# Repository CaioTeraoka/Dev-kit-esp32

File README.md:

# Dev Kit ESP32
This project is a board that was made with the purpose of being used to create and test simples projects using ESP32 DevKit. It was made to enthusiasts to have a complete board to play and have fun learning about ESP32. 

## Specifications:
**Power** - 5V <br>
**Stackup:**
1. Signal + 3.3V
2. Ground

## Main Components
- ESP32 DevKit <br>
- Buzzer <br>
- LEDs <br>
- Buttons <br>
- RGB LEDs <br>
- SPI Pin Headers <br>
- I2C Pin Headers <br>
- ADC Pin Headers <br>
- DAC Pin Headers <br>
- USART Pin Headers <br>
- PWM Pin Headers <br>

## 3D Model
 <br>

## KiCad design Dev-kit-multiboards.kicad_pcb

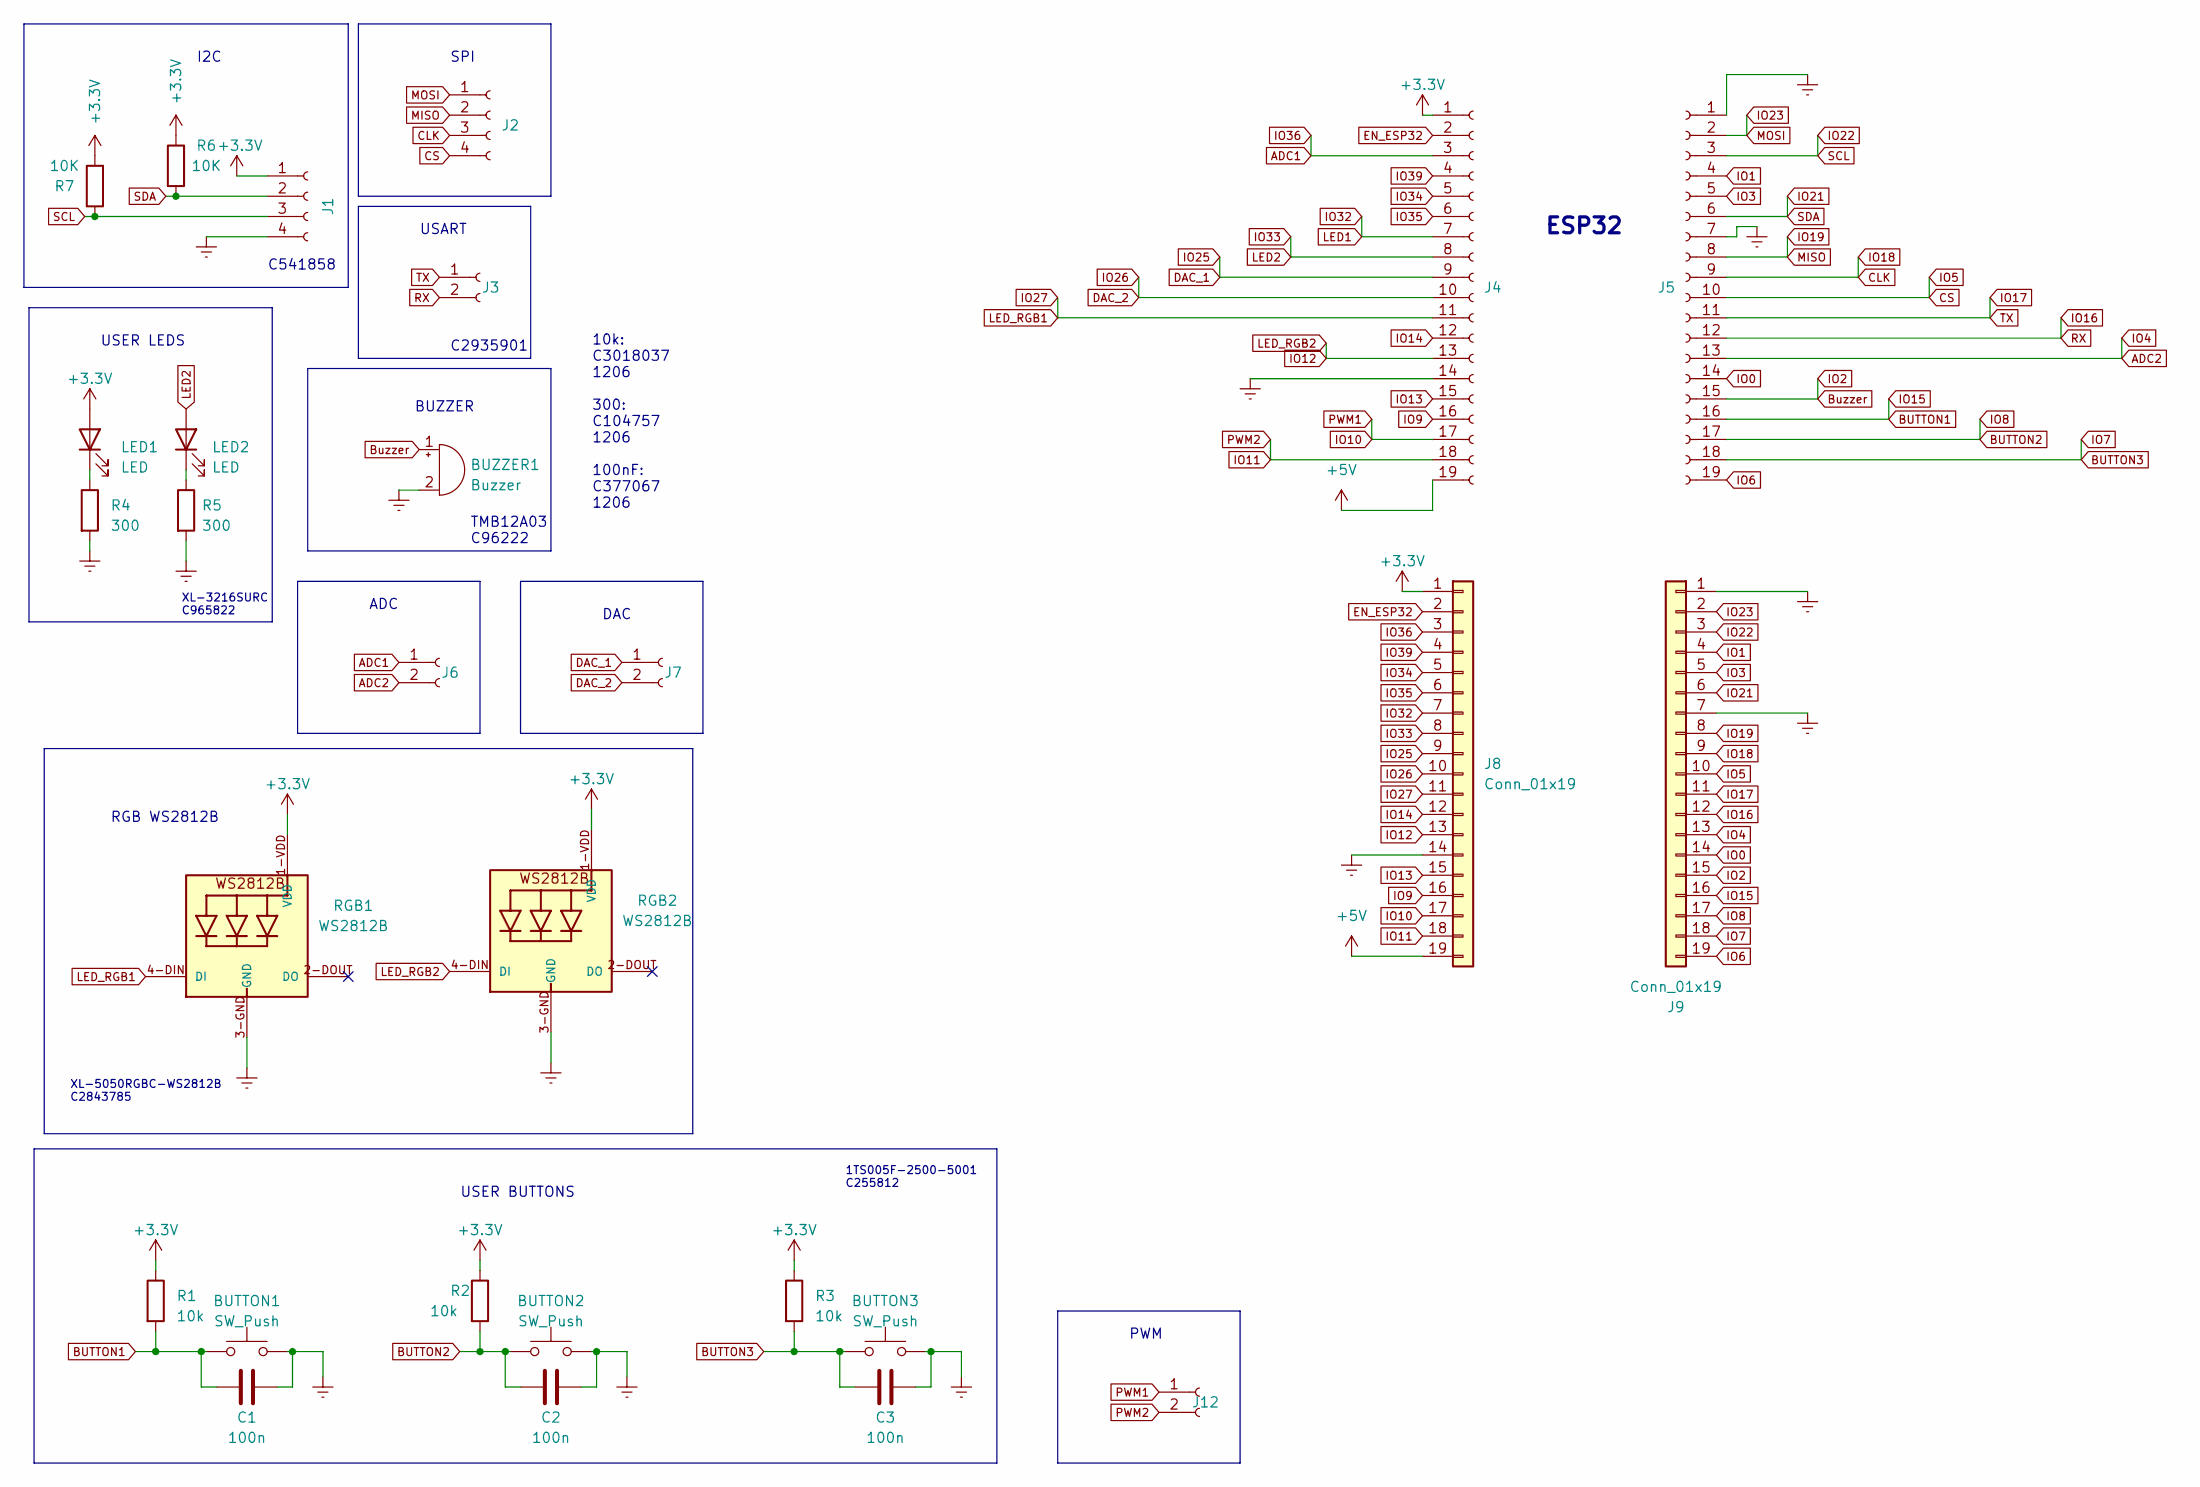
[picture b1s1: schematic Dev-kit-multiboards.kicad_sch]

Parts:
BUTTON1, BUTTON2, BUTTON3: SW_Push; SW_Push_1P1T_NO_6x6mm_H9.5mm
BUZZER1: Buzzer; Buzzer_12x9.5RM7.6
C1, C2, C3: 100n; C_1206_3216Metric
J1, J2: Conn_01x04_Socket; PinHeader_1x04_P2.54mm_Vertical
J3, J6, J7, J12: Conn_01x02_Socket; PinHeader_1x02_P2.54mm_Vertical
J4, J5: Conn_01x19_Socket; PinSocket_1x19_P2.54mm_Vertical
J8, J9: Conn_01x19; PinHeader_1x19_P2.54mm_Vertical
LED1, LED2: LED; LED_1206_3216Metric
R1, R2, R3: 10k; R_1206_3216Metric
R4, R5: 300; R_1206_3216Metric
R6, R7: 10K; R_1206_3216Metric
RGB1, RGB2: WS2812B

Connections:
+3.3V: J1.1, J4.1, J8.1, LED1.2 (A), R1.1, R2.1, R3.1, R6.1, R7.2, RGB1.1-VDD (VDD), RGB2.1-VDD (VDD)
+5V: J4.19, J8.19; also elsewhere on the board
ADC1: J4.3, J6.1, J8.3
ADC2: J5.13, J6.2, J9.13
BUTTON1: BUTTON1.1, C1.1, J5.16, J9.16, R1.2
BUTTON2: BUTTON2.1, C2.1, J5.17, J9.17, R2.2
BUTTON3: BUTTON3.1, C3.1, J5.18, J9.18, R3.2
CLK: J2.3, J5.9, J9.9
CS: J2.4, J5.10, J9.10
DAC_1: J4.9, J7.1, J8.9
DAC_2: J4.10, J7.2, J8.10
EN_ESP32: J4.2, J8.2
Earth: BUTTON1.2, BUTTON2.2, BUTTON3.2, BUZZER1.2 (+), C1.2, C2.2, C3.2, J1.4, J4.14, J5.1, J5.7, J8.14, J9.1, J9.7, R4.2, R5.2, RGB1.3-GND (GND), RGB2.3-GND (GND); also elsewhere on the board
IO0: J5.14, J9.14
IO1: J5.4, J9.4
IO3: J5.5, J9.5
IO6: J5.19, J9.19
IO9: J4.16, J8.16
IO10: J4.17, J8.17, J12.1
IO11: J4.18, J8.18, J12.2
IO12: J4.13, J8.13, RGB2.4-DIN (DI)
IO13: J4.15, J8.15
IO14: J4.12, J8.12
IO16: J3.2, J5.12, J9.12
IO17: J3.1, J5.11, J9.11
IO19: J2.2, J5.8, J9.8
IO21: J1.2, J5.6, J9.6, R6.2
IO22: J1.3, J5.3, J9.3, R7.1
IO23: J2.1, J5.2, J9.2
IO27: J4.11, J8.11, RGB1.4-DIN (DI)
IO32: J4.7, J8.7
IO33: J4.8, J8.8, LED2.2 (A)
IO34: J4.5, J8.5
IO35: J4.6, J8.6
IO39: J4.4, J8.4
unnamed: LED1.1 (K), R4.1
unnamed: LED2.1 (K), R5.1

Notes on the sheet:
ADC
TMB12A03 C96222
DAC
1TS005F-2500-5001 C255812
SPI
I2C
XL-3216SURC C965822
C541858
USART
PWM
BUZZER
ESP32
C2935901
USER LEDS
XL-5050RGBC-WS2812B C2843785
USER BUTTONS
10k: C3018037 1206 300: C104757 1206 100nF: C377067 1206
RGB WS2812B

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
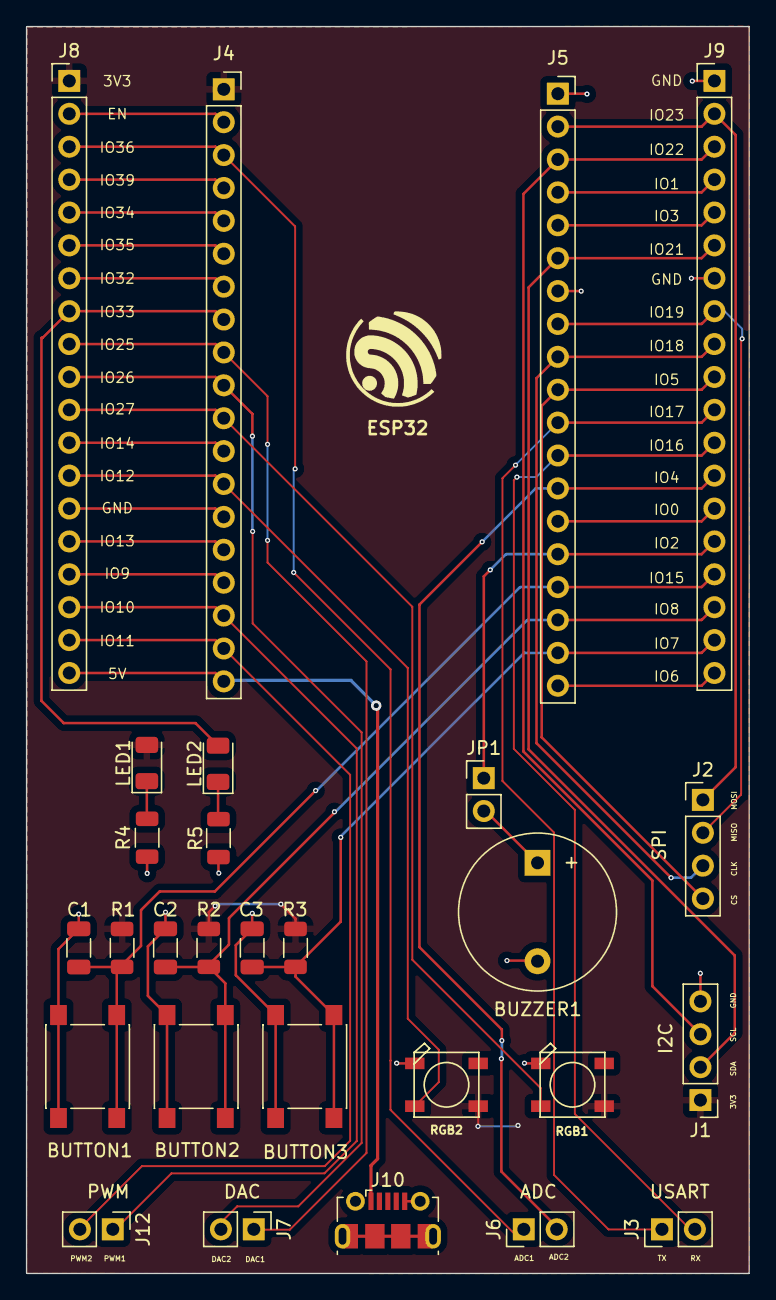
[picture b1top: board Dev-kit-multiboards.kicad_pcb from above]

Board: 2 copper layers, 55.8 x 96.3 mm, 28 parts (0 on the bottom side), 39 nets.

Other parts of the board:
J10: USB_B_Micro; USB_Micro-B_Molex-105017-0001
JP1: Jumper_2_Bridged; PinHeader_1x02_P2.54mm_Vertical

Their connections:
+5V: J10.1 (VBUS); also elsewhere on the board
Earth: J10.5 (GND), J10.6 (Shield); also elsewhere on the board

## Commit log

2023-07-05 Project begin
2023-07-05 component placement
2023-07-06 Component placement ESP32
2023-07-07 Final version
